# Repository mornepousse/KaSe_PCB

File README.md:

# KaSe – Keyboard Dev Kit

This repository contains the KiCad project and resources for the KaSe keyboard, a compact, column-staggered layout inspired by the Atreus62.

## Project overview

KaSe is designed to be:
- ergonomic, with a compact and column-oriented layout;
- DIY‑friendly, using a single PCB and common components;
- easy to customize (firmware, keymap, and hardware variations).

## Photos

### Main view

Assembled KaSe keyboard with switches and keycaps installed. This picture gives an overview of the final form factor and layout.

### Top view – PCB

Top‑side view of the PCB showing:
- board outline,
- switch positions,
- locations of main components and connectors.

### Routing details

Close‑up of the PCB routing, highlighting:
- main traces and vias,
- matrix rows/columns and power traces,
- silkscreen details and graphics.

### Bottom view

Underside of the PCB or assembly, showing:
- copper pours and ground planes,
- pads and vias,
- possible logos and fabrication information.

## Repository structure

- `Old/` – Legacy Atreus62 project kept for reference.
- `V2/KaSe/` – Current KaSe PCB KiCad project (schematic, PCB, libraries, production files).
- `V2/schematic.crv3d` – 3D/MCAD resources related to the project.
- `README.md` – Project documentation (this file).

## Main KiCad files (KaSe)

Inside `V2/KaSe/`:
- `KaSe.kicad_sch` / `KaSe.sch` – keyboard schematic.
- `KaSe.kicad_pcb` – PCB layout for KaSe.
- `Gerbers/` – production files for PCB manufacturing.
- `footprints.pretty/`, `key.pretty/`, `MaeLid.pretty/`, `PMW3360.pretty/`, `NRF24L01_/` – custom footprints and symbols used in the design.
- `KaSe.kicad_pro` / `KaSe.pro` – KiCad project files.

## Opening the project in KiCad

1. Clone the repository:
	```bash
	git clone https://github.com/mornepousse/KaSe_PCB.git
	cd KaSe_PCB
	```
2. Open KiCad.
3. Open the project file `V2/KaSe/KaSe.kicad_pro`.
4. From KiCad, open the schematic (`KaSe.kicad_sch`) and the PCB (`KaSe.kicad_pcb`).

## PCB fabrication

Gerber files for manufacturing are located in `V2/KaSe/Gerbers/`.

Typical steps:
- Zip the contents of `V2/KaSe/Gerbers/`.
- Upload the ZIP archive to your PCB manufacturer (e.g. JLCPCB).
- Check the PCB preview and confirm the order.

## License and usage

Unless otherwise specified in this repository, this project is provided for personal, experimental, and educational use.  
Please credit the original project if you publish or derive from this design.

---

# KaSe – Kit de développement de clavier

Ce dépôt contient le projet KiCad et les ressources nécessaires pour le clavier KaSe, un clavier compact à colonnes inspiré de l’Atreus62.

## Présentation du projet

Le KaSe est conçu pour être :
- ergonomique, avec une disposition compacte et en colonnes ;
- adapté au DIY, avec un seul PCB et des composants courants ;
- facilement personnalisable (firmware, disposition des touches, variantes matérielles).

## Photos

### Vue principale

Clavier KaSe assemblé avec les switchs et les keycaps installés. Cette photo donne une idée du format final et de la disposition.

### Vue du dessus – PCB

Vue du PCB côté composants montrant :
- le contour de la carte,
- l’implantation des switchs,
- les emplacements des principaux composants et connecteurs.

### Détails du routage

Gros plan sur le routage du PCB mettant en avant :
- les pistes et vias principaux,
- les lignes du matrix (rangées/colonnes) et l’alimentation,
- les détails de sérigraphie et éléments graphiques.

### Vue du dessous

Vue de l’arrière du PCB ou de l’assemblage, montrant :
- les plans de masse et surfaces cuivrées,
- les pastilles et vias,
- les logos et informations de fabrication éventuels.

## Structure du dépôt

- `Old/` – Ancien projet Atreus62 conservé comme référence.
- `V2/KaSe/` – Projet KiCad actuel du PCB KaSe (schéma, PCB, bibliothèques, fichiers de production).
- `V2/schematic.crv3d` – Ressources 3D/CAO liées au projet.
- `README.md` – Documentation du projet (ce fichier).

## Fichiers KiCad principaux (KaSe)

Dans `V2/KaSe/` :
- `KaSe.kicad_sch` / `KaSe.sch` – schémas du clavier.
- `KaSe.kicad_pcb` – routage du PCB KaSe.
- `Gerbers/` – fichiers de production pour la fabrication du PCB.
- `footprints.pretty/`, `key.pretty/`, `MaeLid.pretty/`, `PMW3360.pretty/`, `NRF24L01_/` – bibliothèques de footprints et symboles spécifiques.
- `KaSe.kicad_pro` / `KaSe.pro` – fichiers de projet KiCad.

## Ouvrir le projet dans KiCad

1. Cloner le dépôt :
	```bash
	git clone https://github.com/mornepousse/KaSe_PCB.git
	cd KaSe_PCB
	```
2. Ouvrir KiCad.
3. Charger le projet `V2/KaSe/KaSe.kicad_pro`.
4. Depuis KiCad, ouvrir le schéma (`KaSe.kicad_sch`) puis le PCB (`KaSe.kicad_pcb`).

## Fabrication du PCB

Les fichiers Gerber sont dans `V2/KaSe/Gerbers/`.

Étapes typiques :
- Compresser le contenu de `V2/KaSe/Gerbers/` dans une archive `.zip`.
- Importer cette archive sur le site de ton fabricant de PCB (par ex. JLCPCB).
- Vérifier la prévisualisation puis valider la commande.

## Licence et utilisation

Sauf indication contraire dans ce dépôt, ce projet est fourni pour un usage personnel, expérimental et éducatif.  
Merci de mentionner la source si tu republies ou dérives ce design.

Mae Keyboard DEV Kit version

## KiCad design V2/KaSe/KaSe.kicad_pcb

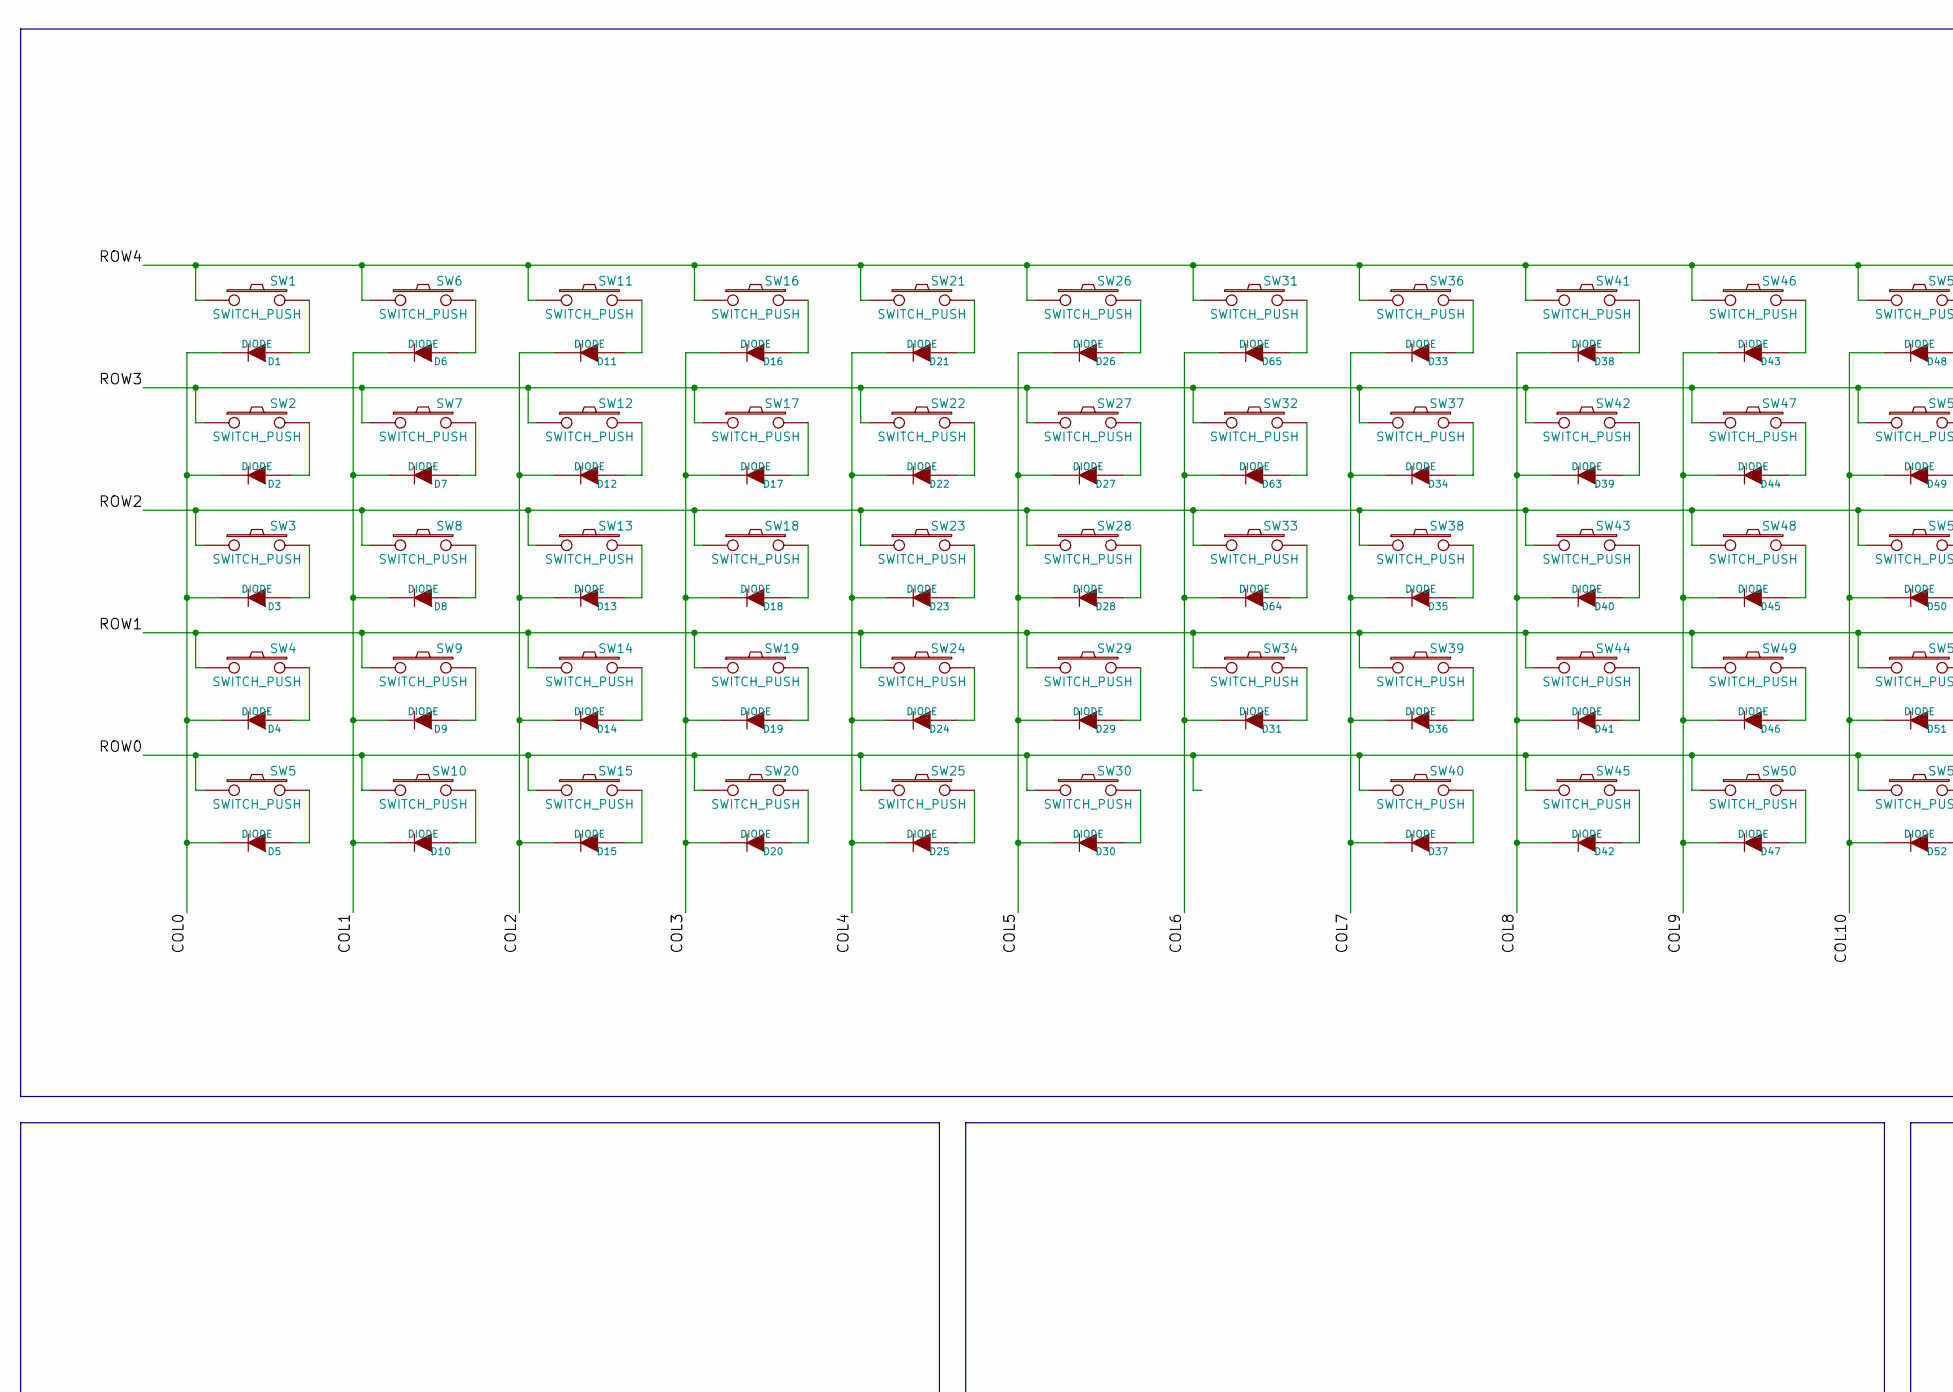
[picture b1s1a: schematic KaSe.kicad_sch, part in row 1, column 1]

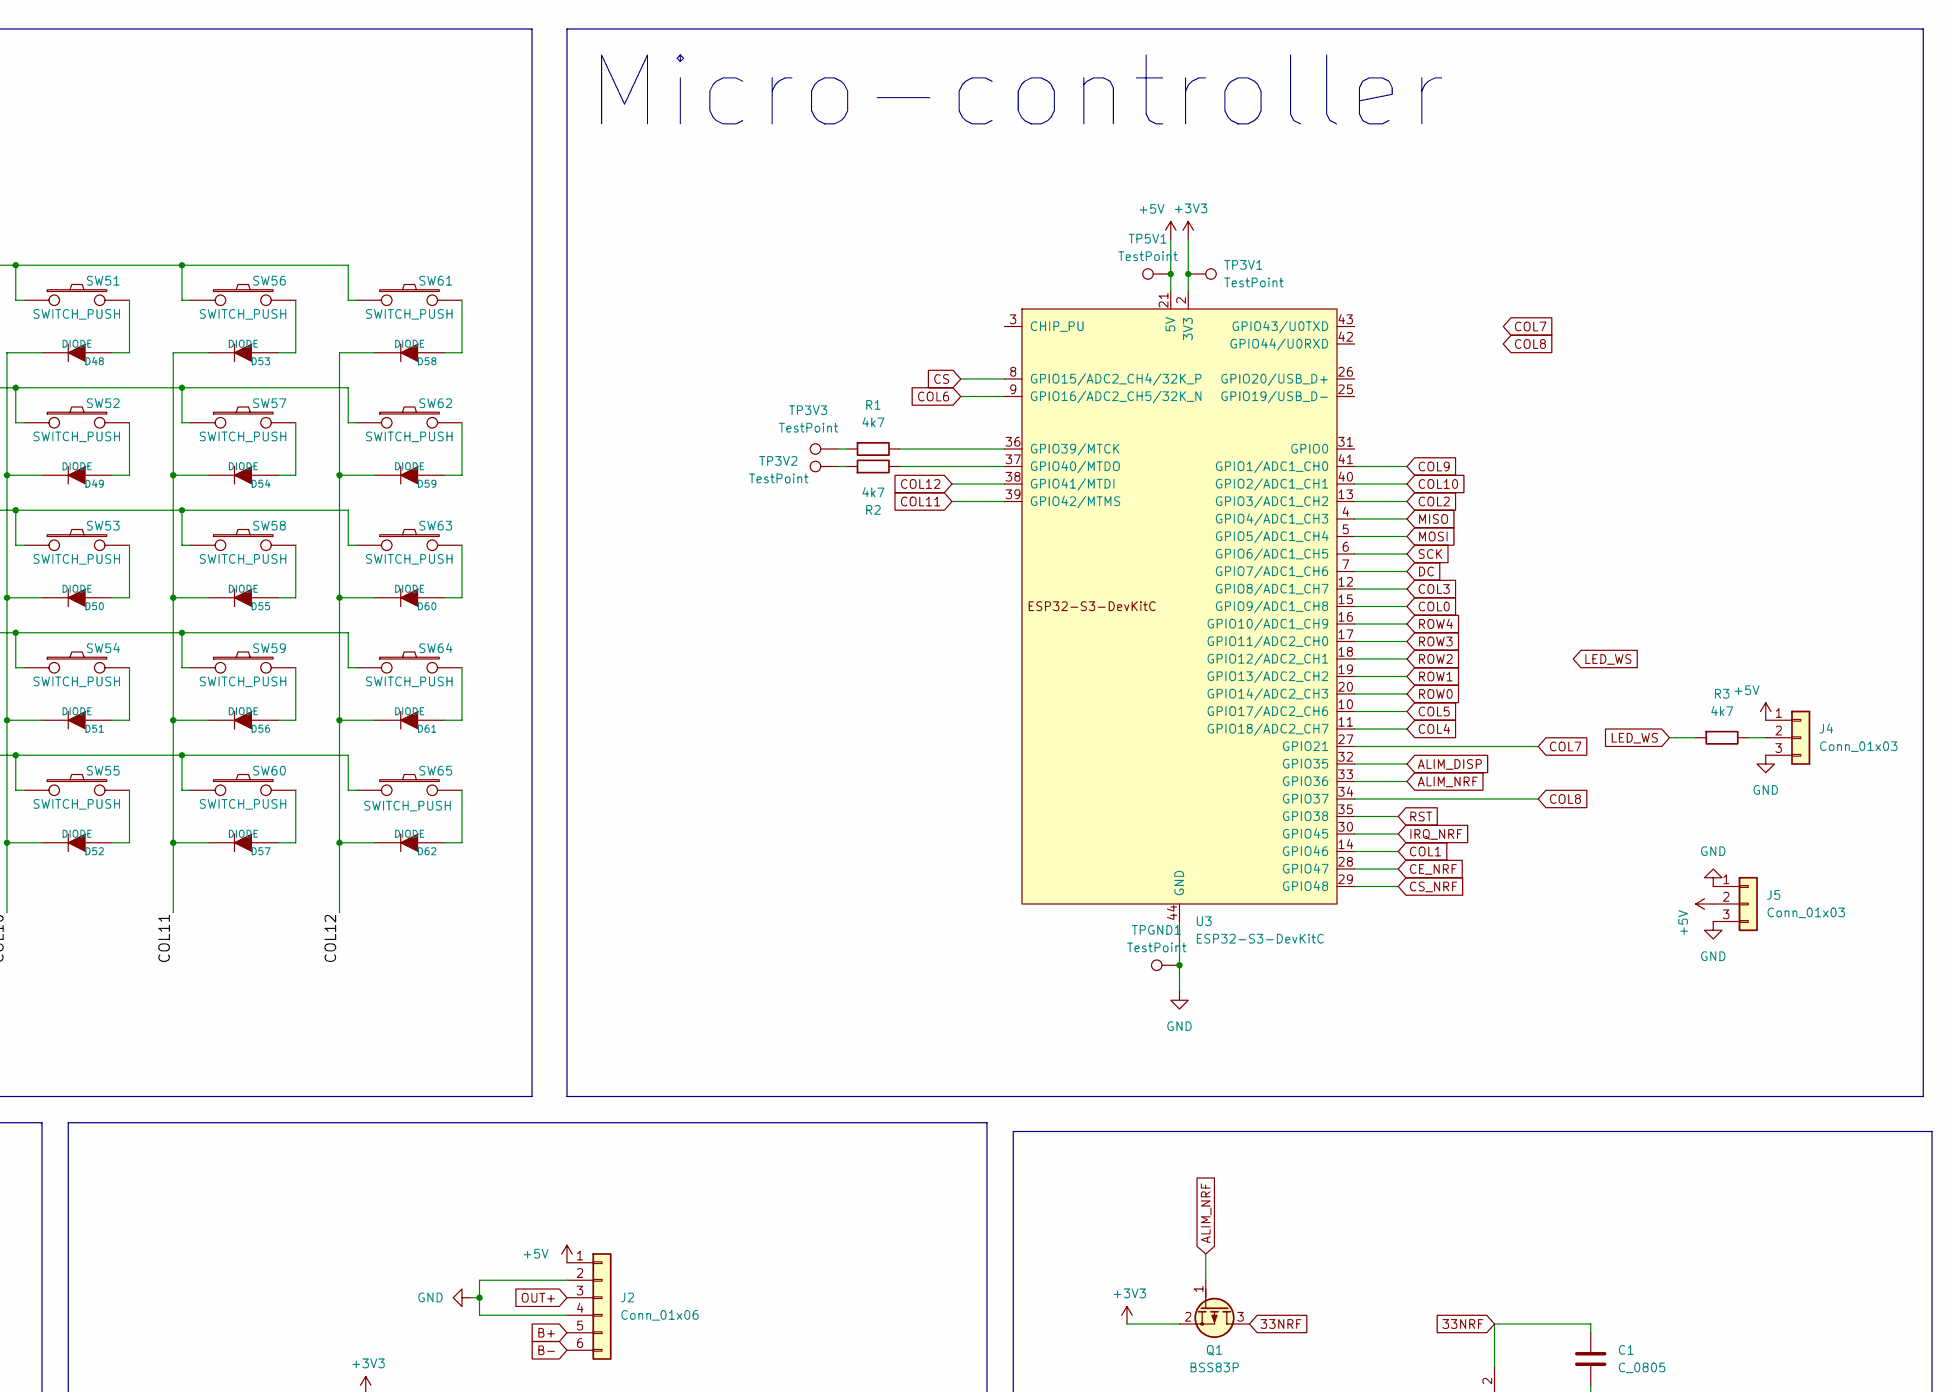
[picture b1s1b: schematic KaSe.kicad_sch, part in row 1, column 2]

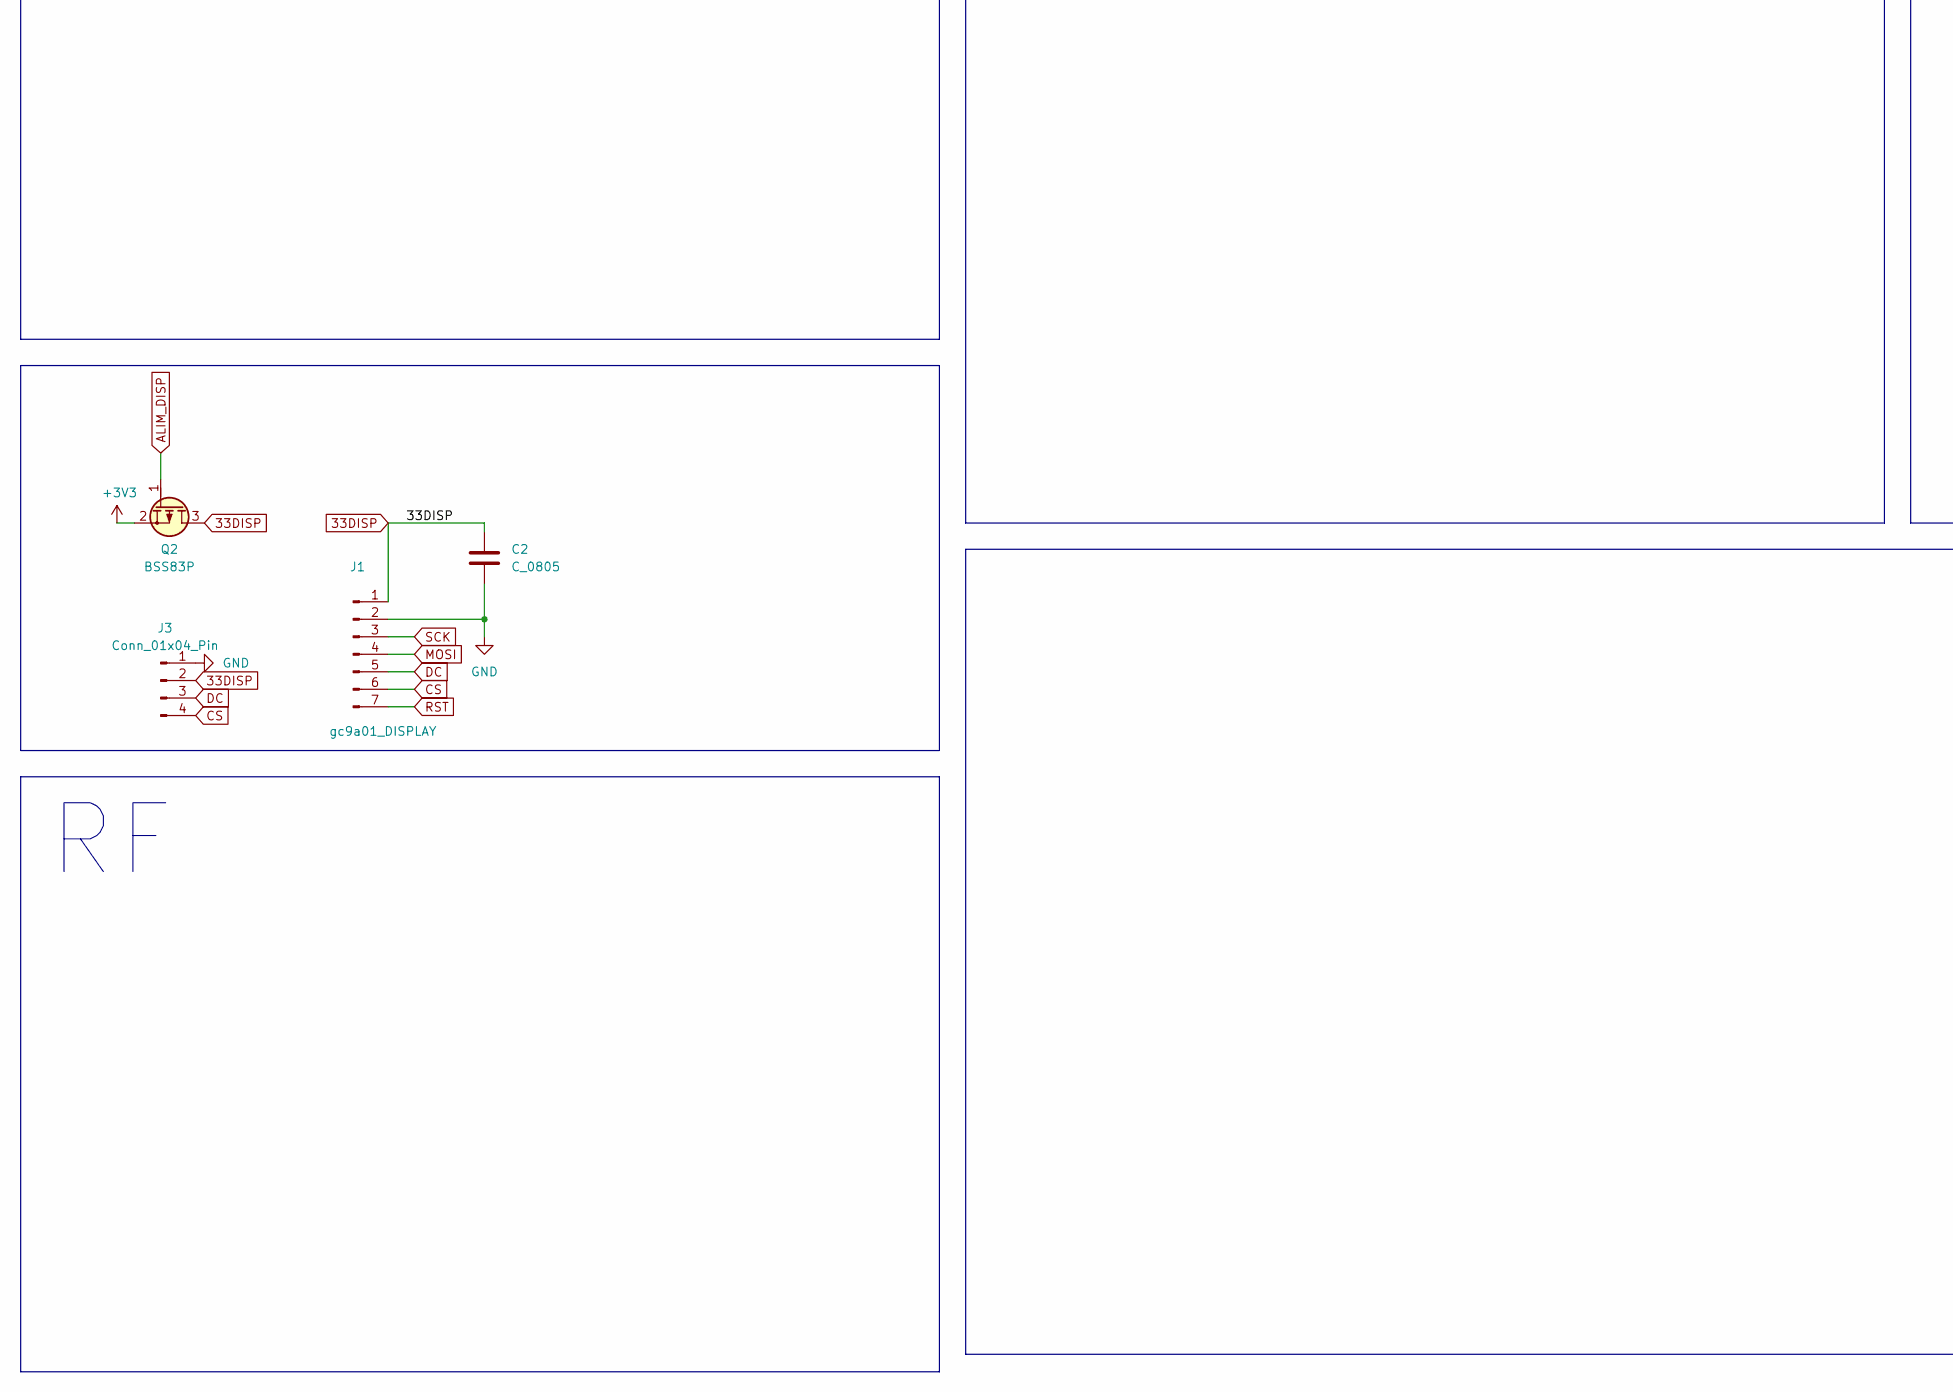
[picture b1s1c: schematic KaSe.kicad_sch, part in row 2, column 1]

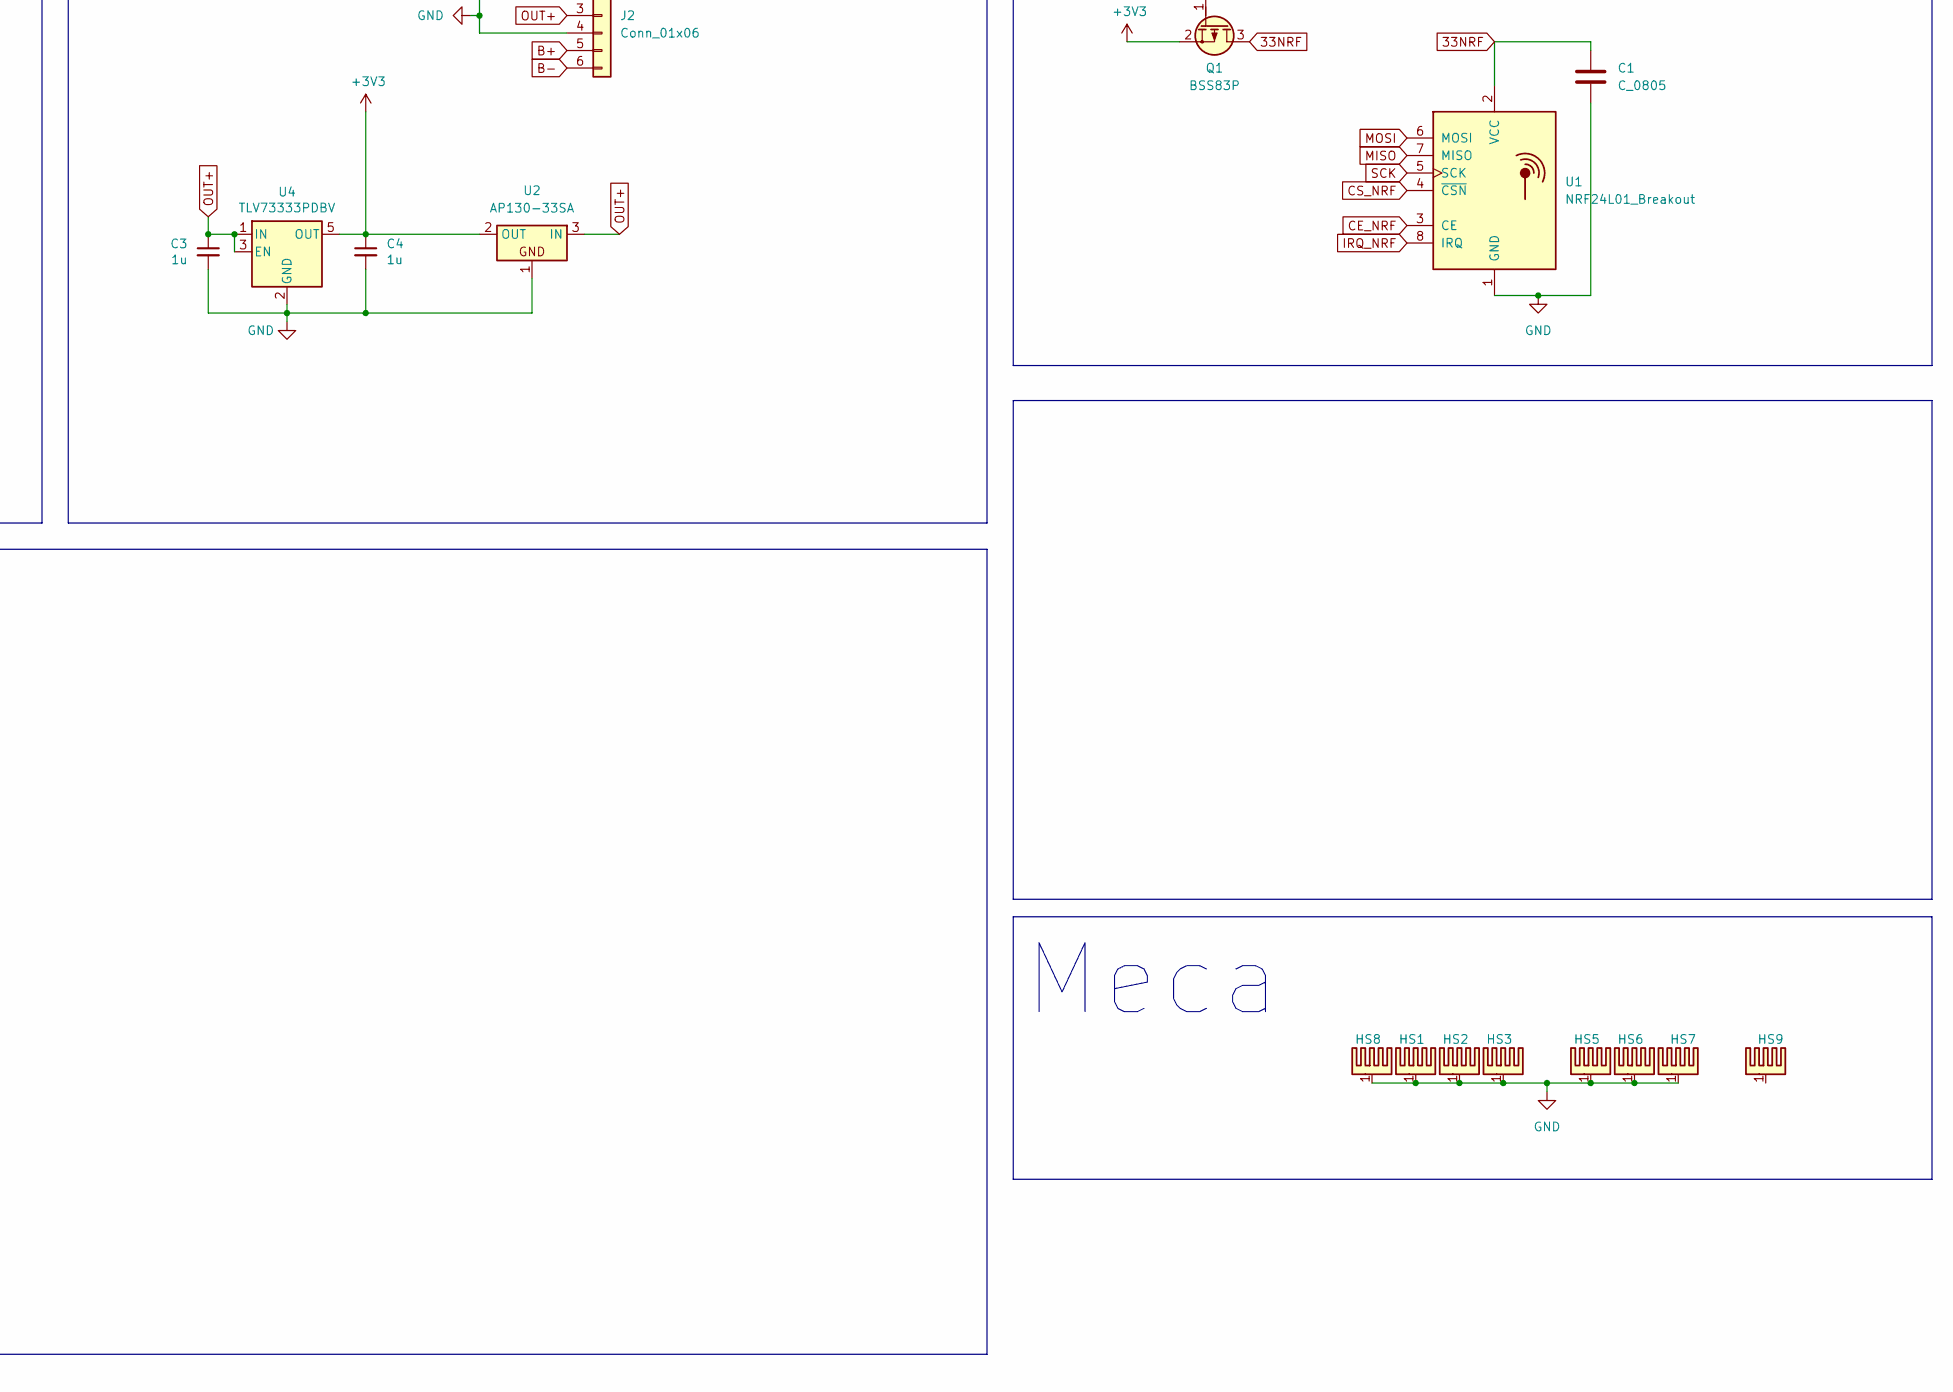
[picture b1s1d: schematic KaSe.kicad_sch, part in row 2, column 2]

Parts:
C1, C2: C_0805; C_0805_2012Metric
C3, C4: 1u; C_0805_2012Metric; LCSC C52923
D1, D2, D3, D4, D5, D6, D7, D8, D9, D10, D11, D12, D13, D14, D15, D16, D17, D18, D19, D20, D21, D22, D23, D24, D25, D26, D27, D28, D29, D30, D31, D33, D34, D35, D36, D37, D38, D39, D40, D41, D42, D43, D44, D45, D46, D47, D48, D49, D50, D51, D52, D53, D54, D55, D56, D57, D58, D59, D60, D61, D62, D63, D64, D65: DIODE; D_SOD-123; JLCPCB_Parts C8598
HS1, HS2, HS3, HS5, HS6, HS7, HS8: Heatsink_Pad; TestPoint_Loop_D3.80mm_Drill2.8mm
HS9: kicad; KiCad-Logo2_5mm_SilkScreen
J1: gc9a01_DISPLAY; PinHeader_1x07_P2.54mm_Vertical
J2: Conn_01x06; TP4056-18650
J3: Conn_01x04_Pin; PinHeader_1x04_P2.54mm_Vertical
J4, J5: Conn_01x03; PinSocket_1x03_P2.54mm_Vertical
Q1, Q2: BSS83P; SOT-23
R1, R2, R3: 4k7; R_Axial_DIN0207_L6.3mm_D2.5mm_P10.16mm_Horizontal
SW1, SW2, SW3, SW4, SW5, SW6, SW7, SW8, SW9, SW10, SW11, SW12, SW13, SW14, SW15, SW16, SW17, SW18, SW19, SW20, SW21, SW22, SW23, SW24, SW25, SW26, SW27, SW28, SW29, SW30, SW31, SW32, SW33, SW34, SW36, SW37, SW38, SW39, SW40, SW41, SW42, SW43, SW44, SW45, SW46, SW47, SW48, SW49, SW50, SW51, SW52, SW53, SW54, SW55, SW56, SW57, SW58, SW59, SW60, SW61, SW62, SW63, SW64, SW65: SWITCH_PUSH; SW_Cherry_MX_1.00u_PCB
TP3V1, TP5V1: TestPoint; TestPoint_Pad_2.5x2.5mm
TP3V2, TP3V3: TestPoint; TestPoint_THTPad_D2.0mm_Drill1.0mm
TPGND1: TestPoint; TestPoint_Pad_2.5x2.5mm
U1: NRF24L01_Breakout; nRF24L01_Breakout
U2: AP130-33SA; SOT-23
U3: ESP32-S3-DevKitC
U4: TLV73333PDBV; SOT-23-5; LCSC C134139

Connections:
33DISP: C2.1, J1.1, J3.2, Q2.3 (D)
33NRF: C1.1, Q1.3 (D), U1.2 (VCC)
+3V3: C4.1, Q1.2 (S), Q2.2 (S), TP3V1.1, U2.2 (OUT), U3.1 (3V3), U3.2 (3V3), U4.5 (OUT)
+5V: J2.1, J4.1, J5.2, TP5V1.1, U3.21 (5V)
ALIM_DISP: Q2.1 (G), U3.32 (GPIO35)
ALIM_NRF: Q1.1 (G), U3.33 (GPIO36)
B+: J2.5
B-: J2.6
CE_NRF: U1.3 (CE), U3.28 (GPIO47)
COL0: D1.2 (K), D2.2 (K), D3.2 (K), D4.2 (K), D5.2 (K), U3.15 (GPIO9/ADC1_CH8)
COL1: D6.2 (K), D7.2 (K), D8.2 (K), D9.2 (K), D10.2 (K), U3.14 (GPIO46)
COL2: D11.2 (K), D12.2 (K), D13.2 (K), D14.2 (K), D15.2 (K), U3.13 (GPIO3/ADC1_CH2)
COL3: D16.2 (K), D17.2 (K), D18.2 (K), D19.2 (K), D20.2 (K), U3.12 (GPIO8/ADC1_CH7)
COL4: D21.2 (K), D22.2 (K), D23.2 (K), D24.2 (K), D25.2 (K), U3.11 (GPIO18/ADC2_CH7)
COL5: D26.2 (K), D27.2 (K), D28.2 (K), D29.2 (K), D30.2 (K), U3.10 (GPIO17/ADC2_CH6)
COL6: D31.2 (K), D63.2 (K), D64.2 (K), D65.2 (K), U3.9 (GPIO16/ADC2_CH5/32K_N)
COL7: D33.2 (K), D34.2 (K), D35.2 (K), D36.2 (K), D37.2 (K), U3.43 (GPIO43/U0TXD)
COL8: D38.2 (K), D39.2 (K), D40.2 (K), D41.2 (K), D42.2 (K), U3.42 (GPIO44/U0RXD)
COL9: D43.2 (K), D44.2 (K), D45.2 (K), D46.2 (K), D47.2 (K), U3.41 (GPIO1/ADC1_CH0)
COL10: D48.2 (K), D49.2 (K), D50.2 (K), D51.2 (K), D52.2 (K), U3.40 (GPIO2/ADC1_CH1)
COL11: D53.2 (K), D54.2 (K), D55.2 (K), D56.2 (K), D57.2 (K), U3.39 (GPIO42/MTMS)
COL12: D58.2 (K), D59.2 (K), D60.2 (K), D61.2 (K), D62.2 (K), U3.38 (GPIO41/MTDI)
CS: J1.6, J3.4, U3.8 (GPIO15/ADC2_CH4/32K_P)
CS_NRF: U1.4 (~CSN), U3.29 (GPIO48)
DC: J1.5, J3.3, U3.7 (GPIO7/ADC1_CH6)
GND: C1.2, C2.2, C3.2, C4.2, HS1.1, HS2.1, HS3.1, HS5.1, HS6.1, HS7.1, HS8.1, J1.2, J2.2, J2.4, J3.1, J4.3, J5.1, J5.3, TPGND1.1, U1.1 (GND), U2.1, U3.22 (GND), U3.23 (GND), U3.24 (GND), U3.44 (GND), U4.2 (GND)
IRQ_NRF: U1.8 (IRQ), U3.30 (GPIO45)
MISO: U1.7 (MISO), U3.4 (GPIO4/ADC1_CH3)
MOSI: J1.4, U1.6 (MOSI), U3.5 (GPIO5/ADC1_CH4)
unnamed: D1.1 (A), SW1.2
unnamed: D2.1 (A), SW2.2
unnamed: D3.1 (A), SW3.2
unnamed: D4.1 (A), SW4.2
unnamed: D5.1 (A), SW5.2
unnamed: D6.1 (A), SW6.2
unnamed: D7.1 (A), SW7.2
unnamed: D8.1 (A), SW8.2
unnamed: D9.1 (A), SW9.2
unnamed: D10.1 (A), SW10.2
unnamed: D11.1 (A), SW11.2
unnamed: D12.1 (A), SW12.2
unnamed: D13.1 (A), SW13.2
unnamed: D14.1 (A), SW14.2
unnamed: D15.1 (A), SW15.2
unnamed: D16.1 (A), SW16.2
unnamed: D17.1 (A), SW17.2
unnamed: D18.1 (A), SW18.2
unnamed: D19.1 (A), SW19.2
unnamed: D20.1 (A), SW20.2
unnamed: D21.1 (A), SW21.2
unnamed: D22.1 (A), SW22.2
unnamed: D23.1 (A), SW23.2
unnamed: D24.1 (A), SW24.2
unnamed: D25.1 (A), SW25.2
unnamed: D26.1 (A), SW26.2
unnamed: D27.1 (A), SW27.2
unnamed: D28.1 (A), SW28.2
unnamed: D29.1 (A), SW29.2
unnamed: D30.1 (A), SW30.2
unnamed: D31.1 (A), SW34.2
unnamed: D33.1 (A), SW36.2
unnamed: D34.1 (A), SW37.2
unnamed: D35.1 (A), SW38.2
unnamed: D36.1 (A), SW39.2
unnamed: D37.1 (A), SW40.2
unnamed: D38.1 (A), SW41.2
unnamed: D39.1 (A), SW42.2
unnamed: D40.1 (A), SW43.2
unnamed: D41.1 (A), SW44.2
unnamed: D42.1 (A), SW45.2
unnamed: D43.1 (A), SW46.2
unnamed: D44.1 (A), SW47.2
unnamed: D45.1 (A), SW48.2
unnamed: D46.1 (A), SW49.2
unnamed: D47.1 (A), SW50.2
unnamed: D48.1 (A), SW51.2
unnamed: D49.1 (A), SW52.2
unnamed: D50.1 (A), SW53.2
unnamed: D51.1 (A), SW54.2
unnamed: D52.1 (A), SW55.2
unnamed: D53.1 (A), SW56.2
unnamed: D54.1 (A), SW57.2
unnamed: D55.1 (A), SW58.2
unnamed: D56.1 (A), SW59.2
unnamed: D57.1 (A), SW60.2
unnamed: D58.1 (A), SW61.2
unnamed: D59.1 (A), SW62.2
unnamed: D60.1 (A), SW63.2
unnamed: D61.1 (A), SW64.2
unnamed: D62.1 (A), SW65.2
unnamed: D63.1 (A), SW32.2
unnamed: D64.1 (A), SW33.2
unnamed: D65.1 (A), SW31.2
unnamed: J4.2, R3.2
unnamed: R1.1, TP3V3.1
unnamed: R2.1, TP3V2.1
unnamed: R1.2, U3.36 (GPIO39/MTCK)
unnamed: R2.2, U3.37 (GPIO40/MTDO)
OUT+: C3.1, J2.3, U2.3 (IN), U4.1 (IN), U4.3 (EN)
ROW0: SW5.1, SW10.1, SW15.1, SW20.1, SW25.1, SW30.1, SW40.1, SW45.1, SW50.1, SW55.1, SW60.1, SW65.1, U3.20 (GPIO14/ADC2_CH3)
ROW1: SW4.1, SW9.1, SW14.1, SW19.1, SW24.1, SW29.1, SW34.1, SW39.1, SW44.1, SW49.1, SW54.1, SW59.1, SW64.1, U3.19 (GPIO13/ADC2_CH2)
ROW2: SW3.1, SW8.1, SW13.1, SW18.1, SW23.1, SW28.1, SW33.1, SW38.1, SW43.1, SW48.1, SW53.1, SW58.1, SW63.1, U3.18 (GPIO12/ADC2_CH1)
ROW3: SW2.1, SW7.1, SW12.1, SW17.1, SW22.1, SW27.1, SW32.1, SW37.1, SW42.1, SW47.1, SW52.1, SW57.1, SW62.1, U3.17 (GPIO11/ADC2_CH0)
ROW4: SW1.1, SW6.1, SW11.1, SW16.1, SW21.1, SW26.1, SW31.1, SW36.1, SW41.1, SW46.1, SW51.1, SW56.1, SW61.1, U3.16 (GPIO10/ADC1_CH9)
RST: J1.7, U3.35 (GPIO38)
SCK: J1.3, U1.5 (SCK), U3.6 (GPIO6/ADC1_CH5)

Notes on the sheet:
Meca
Micro-controller

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
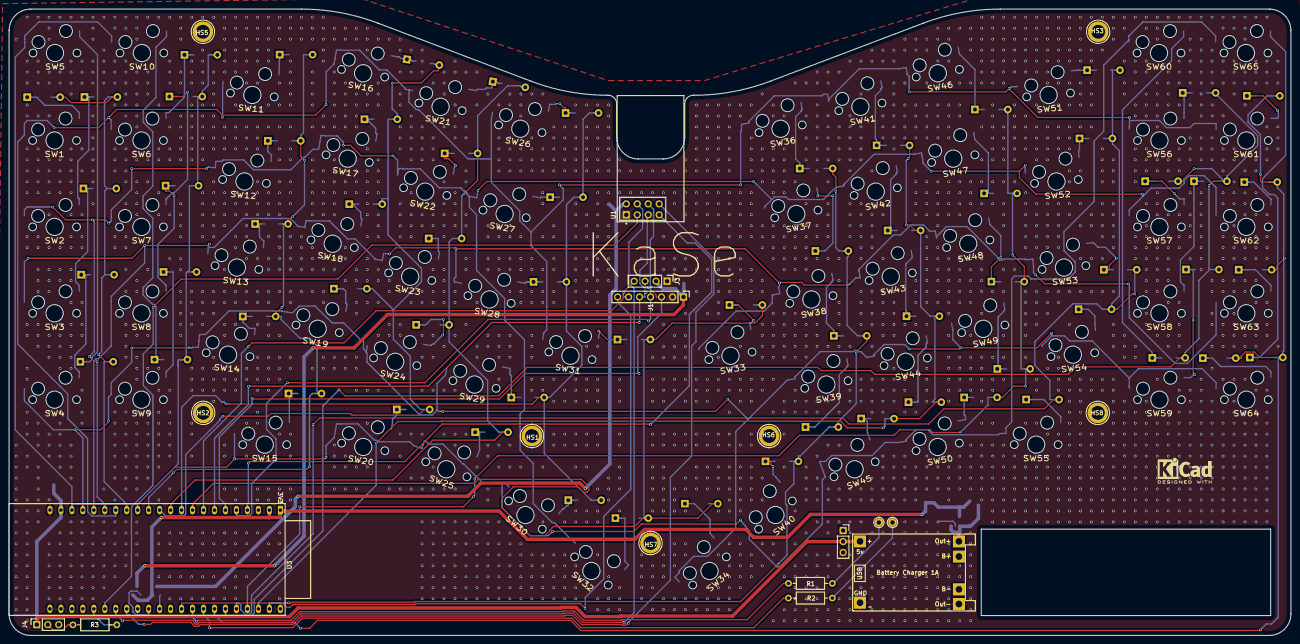
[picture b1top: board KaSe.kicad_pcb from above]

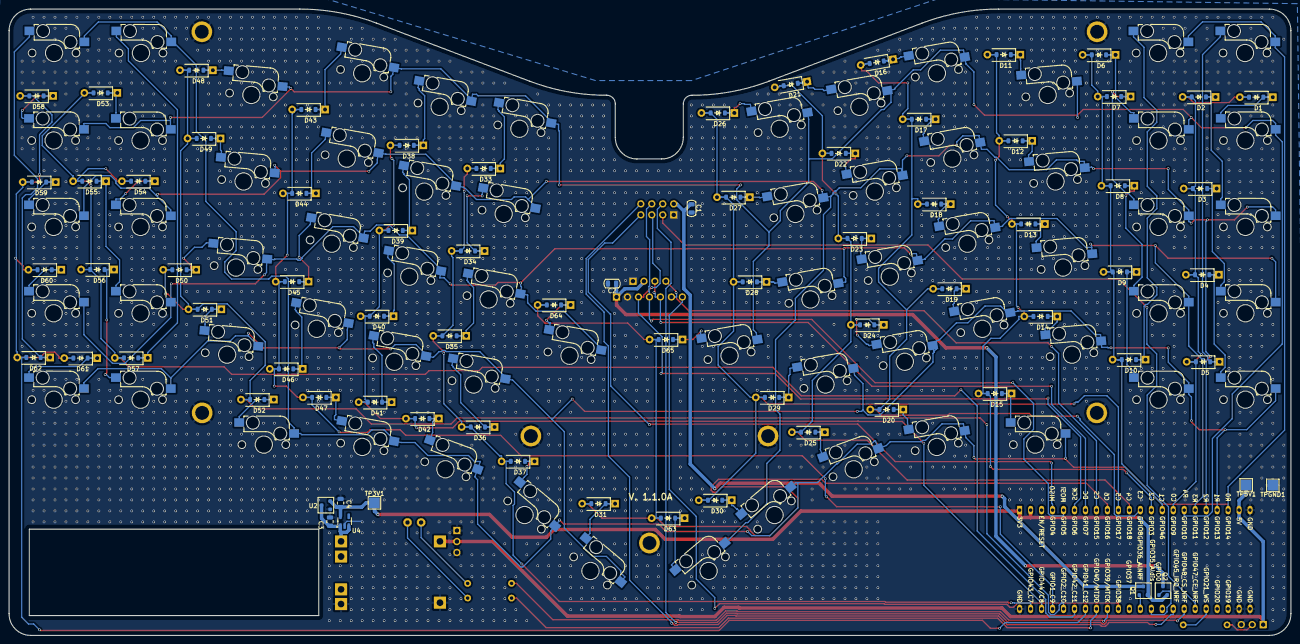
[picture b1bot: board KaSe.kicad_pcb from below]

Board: 2 copper layers, 296.8 x 145.0 mm, 159 parts (75 on the bottom side), 105 nets.

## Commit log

2024-12-10 first
2024-12-11 send JLC
2024-12-11 Update README.md add image
2025-04-21 clean up
2025-05-19 update-integration
2025-05-26 add i2c display ssd1306 and clean up for print
2026-01-08 Initial plan
2026-01-08 Add ROADMAP.md for KaSe V3 "Endgame" version
